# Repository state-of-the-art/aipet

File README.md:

# AiPet

AiPet project aimed to create the AI-enchanced soft robot pet. In general it's an inflated beach
ball which contains a core with electronics and motors inside, controls pressure and position of
the core by teflon strings to move around.

It can hear by mic array, see the world via 2 cameras and use internal speakers to make noise. The
charging is wireless so it can charge itself if can find the properly placed wireless charger.

## Electric schema

Check this document to figure out: [Electric schema](doc/electric_schema.svg)

## Components

* [Sipeed Maix M1W Dock Kit K210 AI+lOT WiFi Development Board RISC-V Dual Core 64bit](https://www.amazon.com/dp/B08HJ8W1WB/)
* [Sipeed Maix Binocular Camera](https://www.amazon.com/dp/B08HH9BYTF/)
* [Sipeed Maix R6+1 Microphone Array](https://www.amazon.com/dp/B08HH799XZ/)
* [Flexible Flat Cable, 24 Pins 0.5mm Pitch 150mm FPC FFC](https://www.amazon.com/dp/B07S191XHZ/)
* [0.5mm Pitch 24 Pins to 24 Pin Extension Connector Aapter FFC FPC](https://www.amazon.com/dp/B07SWR5VP9/)
* [3.7V 2000mAh Lithium Rechargable Battery 1S 3C](https://www.amazon.com/dp/B08T6QS58J/)
* [DC 5V 9V 12V UPS Module Voltage Boost Battery Charge with Protection for Lithium Li-ion 18650 Battery](https://www.amazon.com/dp/B08LZCPVFM/)
* [6x 3V Micro Planetary Reducer Motor (9161C)](https://www.amazon.com/dp/B07N7PY71F)
* [6x custom motor driver](custom/m10_mini_dc_control/)
* [DRV8833 Motor Drive Module 1.5A Dual H Bridge](https://www.amazon.com/dp/B08RMWTDLM/)
* [2x OV2640 Camera Module T-Camera Plus Camera Module ESP32-DOWDQ6 8MB SPRAM with 1/4" OLED Fisheye Lens](https://www.amazon.com/dp/B08FC2FL79/)
* [GY-87 10DOF Module MPU6050 HMC5883L BMP180 Gyroscope Acceleration Compass](https://www.amazon.com/dp/B098JN14XV/)
* [2x Magnetic Speaker 1W 8 Ohm 20x14x3mm](https://www.amazon.com/dp/B0826YMCQ7/)
* [High Power 24V 200mm One-to-Many Long Distance Wireless Charging Pad](https://www.amazon.com/dp/B07QNF6J6Z/)

* [6x MR63ZZ 3x6x2.5mm Rolling Bearing](https://www.amazon.com/dp/B0816CL22H/)
* [16inch Clear Beach Ball](https://www.amazon.com/dp/B0943CCZLQ/)
* [6x Clear Suction Cups](https://www.amazon.com/dp/B07H5QCXR6/)
* Silicone air hose
* FDM 3D Printer

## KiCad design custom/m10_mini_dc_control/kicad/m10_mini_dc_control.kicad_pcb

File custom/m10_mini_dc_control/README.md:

# m10 mini dc control

This control board designed to precisely control the 9161C geared M10 mini motor with extended
shaft.

# Usage

In general you just need to connect the board to your I2C bus and power it with 5V of power (in
theory voltage regulator allows 2.5-5.5V so the motor can work on lower voltages with slower speed).

You will need to modify the `I2C_SLAVE_ADDRESS` in firmware, compile it (or use the predefined one)
and flash to the MK. After that you will be able to use as many motors as you want.

## Firmware

TODO

# Components

* 3V Micro Planetary Reducer Motor (9161C) - target motor with plastic reduction gearbox
* ATTiny 13A MMFR (DFN-10 3x3mm) - microcontroller to interface I2C and control the driver
* DRV8837C DSGR (WSON) - H-bridge driver for the motor
* MIC5365-3.3YMT-TZ (Thin MLF (MT)) - 5V to 3.3V voltage regulator to power the MK and driver logic
* QRE1113GR (100CY) - reflective object sensor to detect the motor rotation
* Various 0201 and 0402 resistors, caps and a LED

* (optional) Electrolitic capacitor to store the rest power from the motor (check driver DS)

## [3V Micro Planetary Reducer Motor (9161C)](https://www.amazon.com/dp/B07N7PY71F)

Price: $1.8 ($9 for 5pc)

### Motor specifications:

* Reduction ratio: 1:171
* Rated torque: 9.8 mN.m
* Maximum torque: 37.2 mN.m

* Rated voltage: 2.5V DC
* No-load current: 40mA
* No-load speed: 92 RPM

* Dimensions: 8x10x12mm (M10 motor)
* Planetary gearbox outer diameter: 9.9mm
* Weight: 4 grams
* Geared motor height: 19.5mm (motor + gear box)
* Output shaft: Gear with an outer diameter of 5.35mm (11 teeth)

### The following measures the motor speed under other voltages:

* Voltage: 3V
  * Current: 42mA
  * Speed: 110 RPM
* Voltage: 3.7V
  * Current: 48mA
  * Speed: 135 RPM
* Voltage: 4.2V
  * Current: 52mA
  * Speed: 154 RPM
* Voltage: 5V
  * Current: 58mA
  * Speed: 180 RPM

# How to order

Just go to your favorite PCB manufacturer and order as many boards as you want.

* [PCBWay](doc/pcbway_order.png)

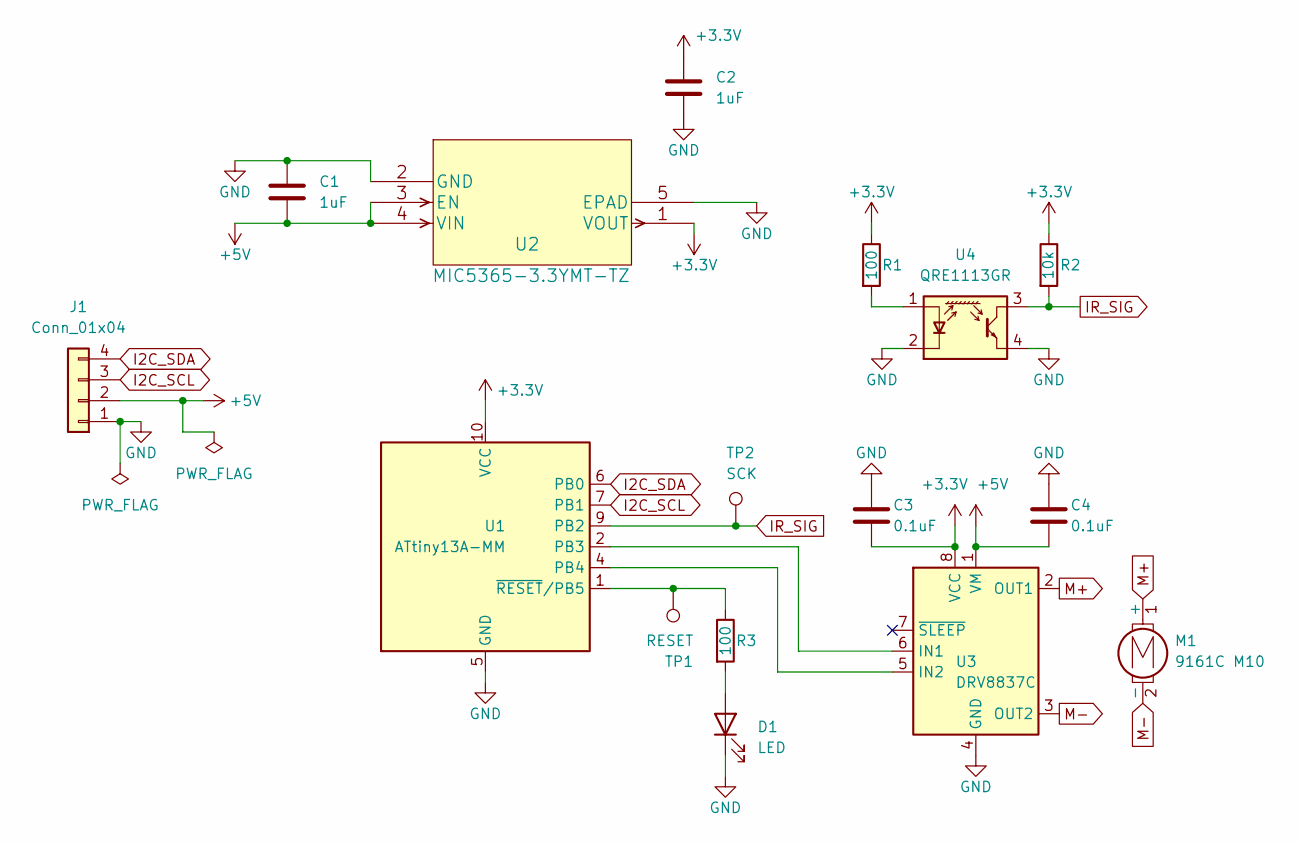
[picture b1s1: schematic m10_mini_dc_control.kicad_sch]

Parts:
C1, C2: 1uF; C_0201_0603Metric
C3, C4: 0.1uF; C_0201_0603Metric
D1: LED; LED_0201_0603Metric
J1: Conn_01x04; PinSocket_1x04_P1.00mm_Vertical
M1: 9161C M10; 9161C-m10-motor
R1: 100; R_0402_1005Metric
R2: 10k; R_0402_1005Metric
R3: 100; R_0201_0603Metric
TP1: RESET; TestPoint_Pad_D1.0mm
TP2: SCK; TestPoint_Pad_D1.0mm
U1: ATtiny13A-MM; DFN-10-1EP_3x3mm_P0.5mm_EP1.75x2.7mm
U2: MIC5365-3.3YMT-TZ
U3: DRV8837C; WSON-8-1EP_2x2mm_P0.5mm_EP0.9x1.6mm
U4: QRE1113GR; OnSemi_CASE100CY

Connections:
+3V3: C2.2, C3.2, R1.1, R2.1, U1.10 (VCC), U2.1 (VOUT), U3.8 (VCC)
+5V: C1.2, C4.2, J1.2, U2.3 (EN), U2.4 (VIN), U3.1 (VM)
GND: C1.1, C2.1, C3.1, C4.1, D1.1 (K), J1.1, U1.5 (GND), U1.11 (GND), U2.2 (GND), U2.5 (EPAD), U3.4 (GND), U3.9 (GND), U4.2 (K), U4.4
I2C_SCL: J1.3, U1.7 (PB1)
I2C_SDA: J1.4, U1.6 (PB0)
IR_SIG: R2.2, TP2.1, U1.9 (PB2), U4.3
M+: M1.1 (+), U3.2 (OUT1)
M-: M1.2 (-), U3.3 (OUT2)
unnamed: D1.2 (A), R3.2
unnamed: R3.1, TP1.1, U1.1 (~RESET/PB5)
unnamed: U1.4 (PB4), U3.5 (IN2)
unnamed: U1.2 (PB3), U3.6 (IN1)
unnamed: R1.2, U4.1 (A)

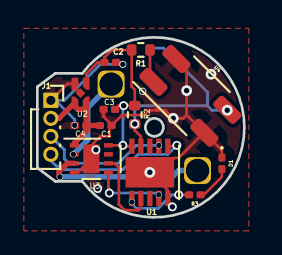
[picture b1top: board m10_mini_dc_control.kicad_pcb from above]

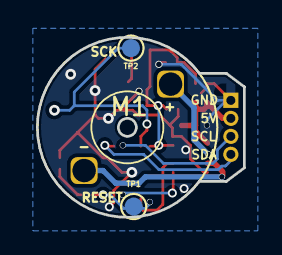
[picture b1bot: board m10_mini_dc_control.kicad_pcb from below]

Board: 2 copper layers, 11.5 x 10.0 mm, 16 parts (3 on the bottom side), 13 nets.

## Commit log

2022-01-18 Added the first documentation and the base model
2022-01-25 Added the custom control boards for the 9161C motor
2022-01-26 Fixed motor control pcb issue with not connected ground
2022-01-26 Made PCB 0.6mm since there is no way to reroute to drill a hole
